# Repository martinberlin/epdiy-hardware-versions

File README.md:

# EPDiy Hardware 

Design files for [EPDiy](https://github.com/vroland/epdiy) controllers, controller variants, display adaptors, and other related hardware.  
See [vroland.github.io/epdiy-hardware/](https://vroland.github.io/epdiy-hardware/) for available hardware.

## What is EPDiy?

Please refer to the [main project repository](https://github.com/vroland/epdiy) for more information.

## Cloning

Make sure to clone recursively, to get hardware library submodules:
```
git clone git@github.com:vroland/epdiy-hardware.git --recursive
# or with http
git clone https://github.com/vroland/epdiy-hardware.git --recursive
```

## Contributing Hardware

Contributions in the form of adapter boards, utilities or epdiy variants are always welcome!
Please submit a PR and make sure your KiCAD project is in the right format, so our automation can build 
the manufacturing files and overview page:

* For every board, the KiCAD project should be given a unique name, and have the same name as the containing folder. 
  Example: `epdiy-v7/epdiy-v7.{kicad_pro,kicad_pcb,kicad_sch}`. 
  An existing KiCAD project can be renamed by selecting `File -> Save As` in the main KiCAD window and saving it to a folder with the new name.
* Unless you *explicitly* specify otherwise, your contribution will be licensed under the Creative Commons Attribution-ShareAlike 4.0 International License.
  Feel free to mention in the README in your project folder how you want to be attributed.
  Please indicate in the PR if you intend to use a different license.
* Each board needs a README.md in it's project folder, which will also appear as description in the presentation page.
  Refer to `epdiy-v7/README.md` for an example.
* If it's a helper or an adapter board, place it in the appropriate `helpers` or `adapters` folder.
* Delete the manufacturing files and keep only the sources.
  Since we generate those automatically, having potentially outdated ones in the repo will be confusing. 
* Add your board to the `BOARDS` list in the root `Makefile`.
  This enables the continuous integration to build the manufacturing files for your board.

## Available Hardware

The full list of available hardware is available at [vroland.github.io/epdiy-hardware/](https://vroland.github.io/epdiy-hardware/).
For each board, we provide:

- Gerber files
- Bill of Materials (BoM)
- Pick & Place Positioning file
- PDF Schematic
- 3D model of the board for use in CAD

## Related repositories

- [Check FastJsonDL](https://github.com/martinberlin/FastJsonDL) a JSON domain language to draw GFX on displays that could be sent from a webservice or from an AI agent.
- [vroland/epdiy](https://github.com/vroland/epdiy)

## Licensing

Unless otherwise specified, the hardware sources provided are licensed under the terms of the Creative Commons Attribution-ShareAlike 4.0 International License.
<a rel="license" href="https://creativecommons.org/licenses/by-sa/4.0/">Creative Commons Attribution-ShareAlike 4.0 International License </a>

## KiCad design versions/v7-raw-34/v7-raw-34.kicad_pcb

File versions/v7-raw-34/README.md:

### Epdiy V7 RAW

The V7 controller iteration is based on the ESP32S3. Highlights of the new board include:

- Much faster updates thanks to the ESP32S3 SOC and the LCD peripheral
- Front light support for Kindle / Kaleido 
- LiPo charging

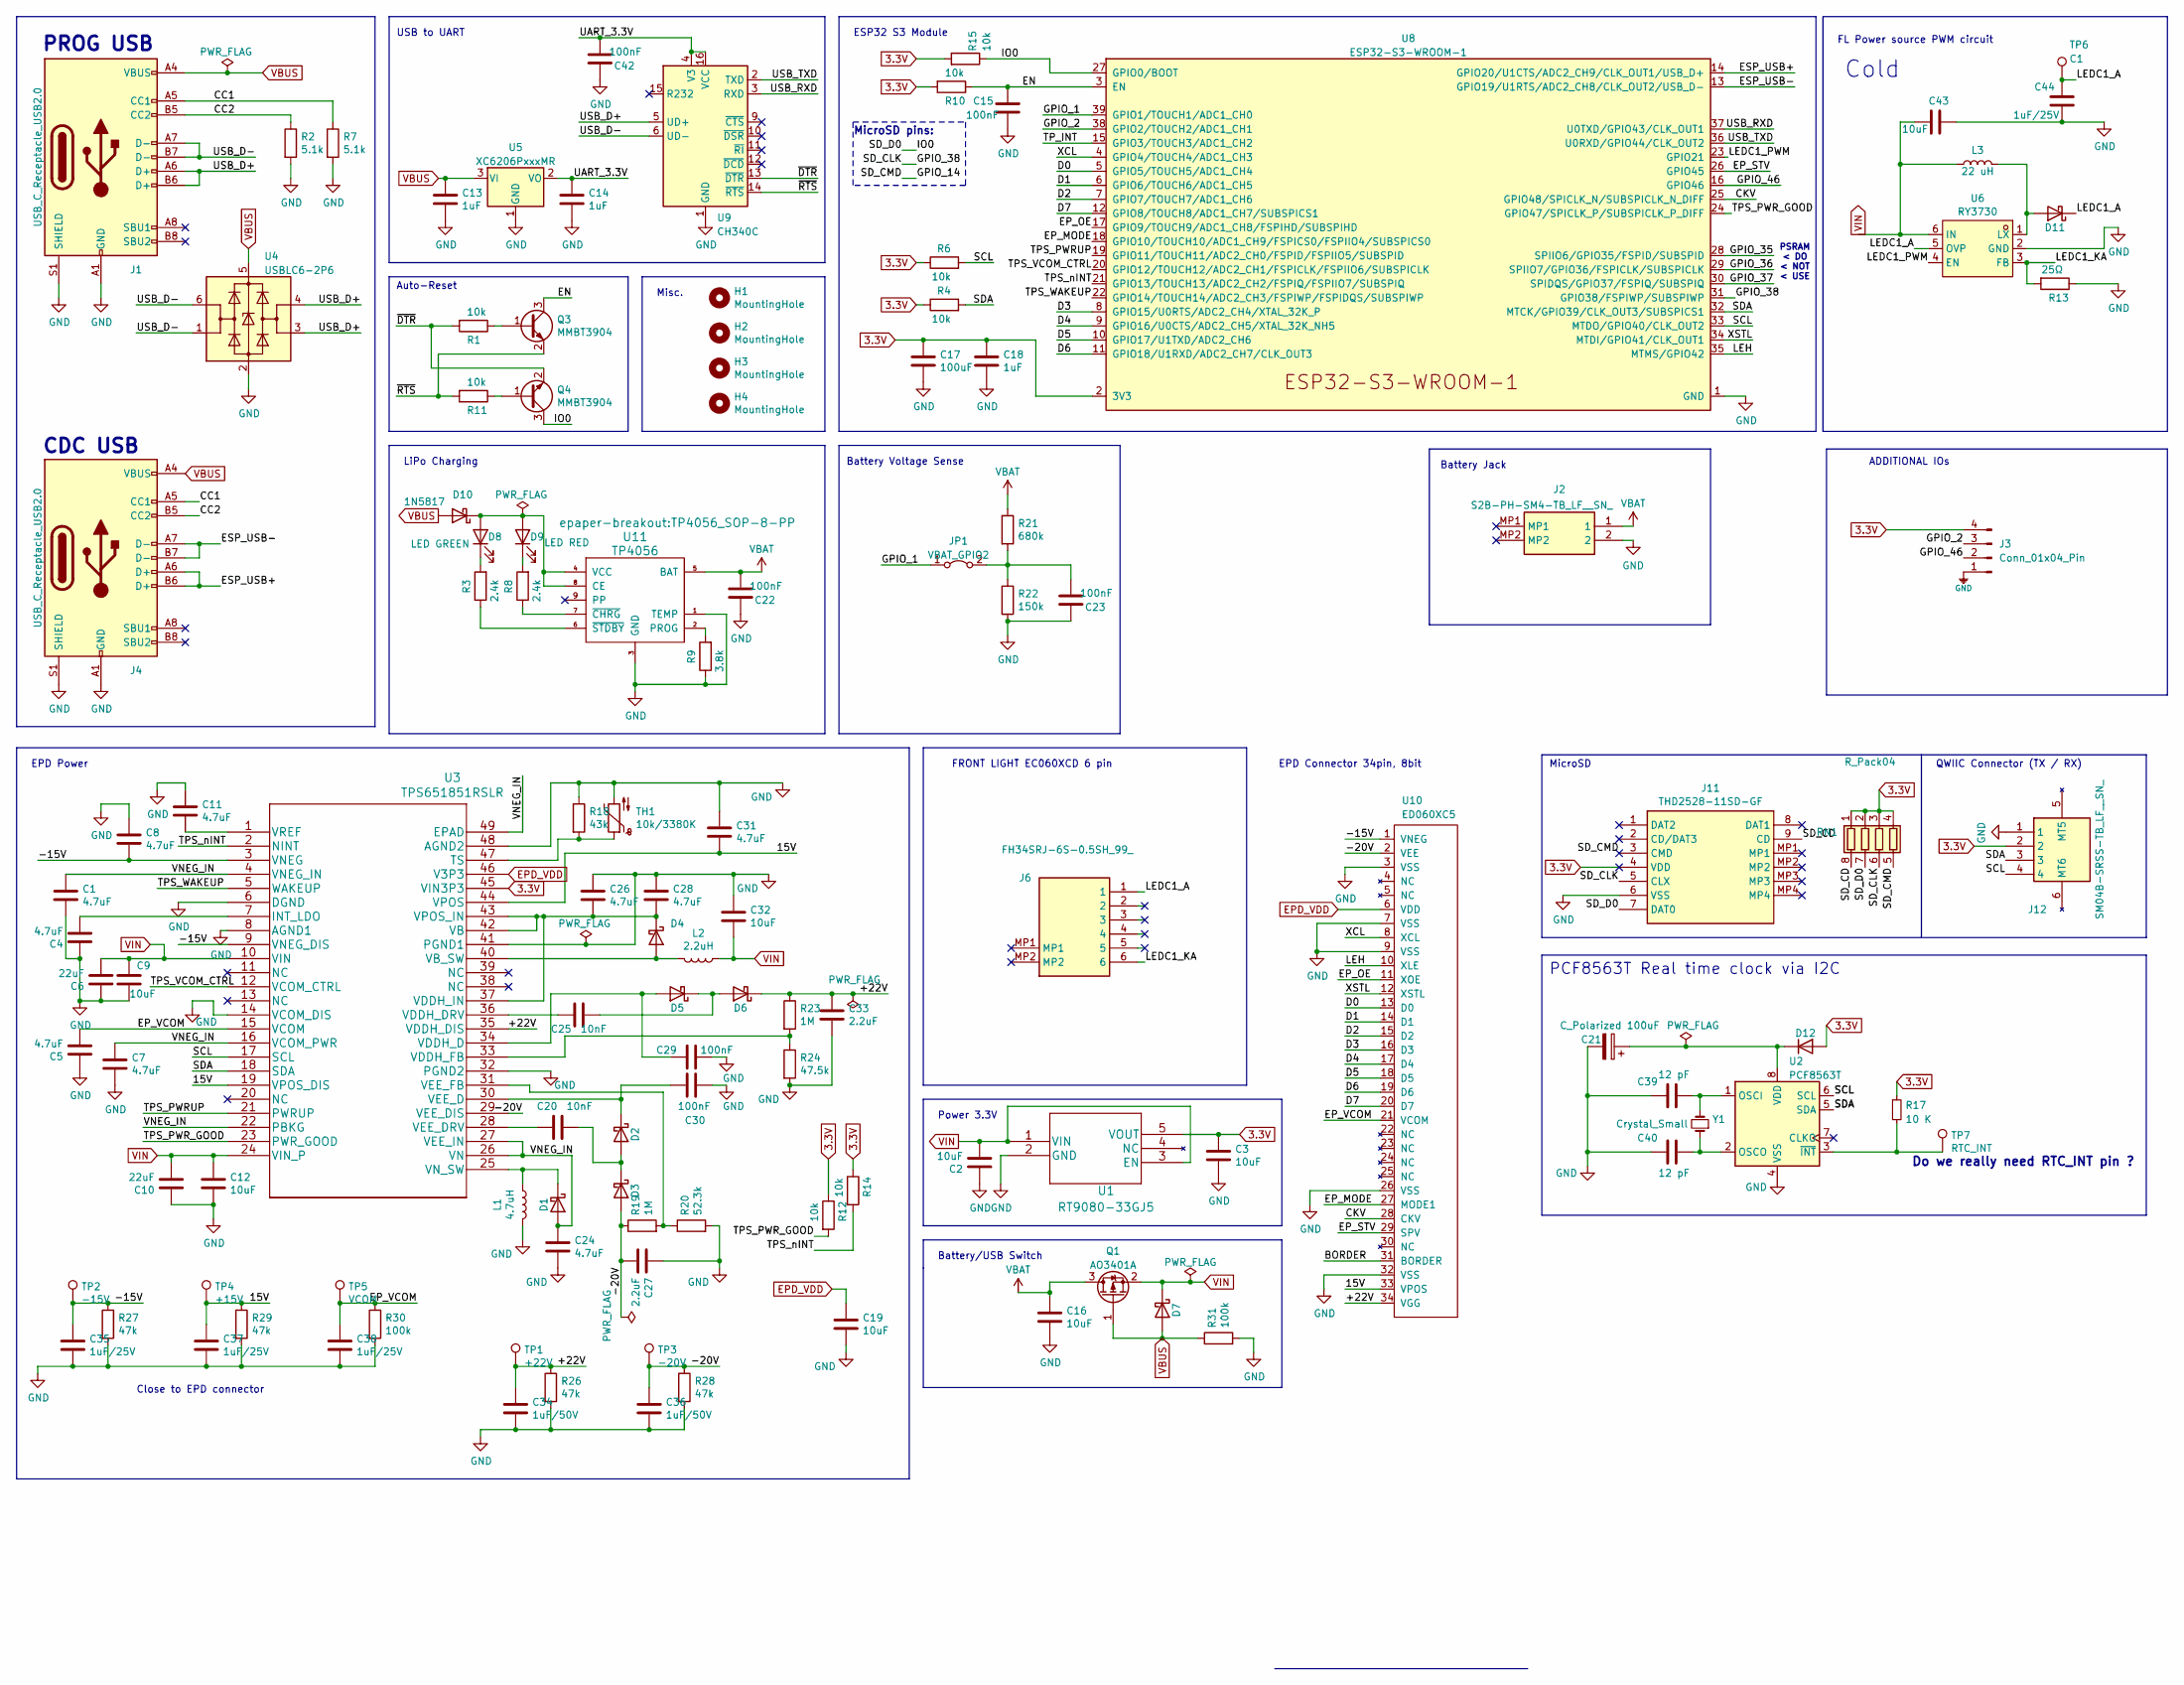
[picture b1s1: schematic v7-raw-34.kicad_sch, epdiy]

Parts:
C1, C4, C5, C7, C8, C11, C24, C26, C28, C31: 4.7uF; C_0805_2012Metric; LCSC C1779
C2, C3, C9, C12, C16, C19, C32, C43: 10uF; C_0805_2012Metric; LCSC C15850
C6, C10: 22uF; C_0805_2012Metric; LCSC C45783
C13, C14, C18: 1uF; C_0805_2012Metric; LCSC C28323
C15, C22, C23, C29, C30, C42: 100nF; C_0805_2012Metric; LCSC C49678
C17: 100uF; CP_EIA-3528-15_AVX-H; LCSC C16133
C20, C25: 10nF; C_0805_2012Metric; LCSC C1710
C21: C_Polarized 100uF; CP_EIA-3528-21_Kemet-B; LCSC C129289
C27, C33: 2.2uF; C_0805_2012Metric; LCSC C49217
C34, C36: 1uF/50V; C_1206_3216Metric; LCSC C1848
C35, C37, C38, C44: 1uF/25V; C_0805_2012Metric; LCSC C28323
C39, C40: 12 pF; C_0603_1608Metric; LCSC C38523
D1, D2, D3, D4, D5, D6, D7, D11: MBR0540; D_SOD-123; LCSC C21353
D8: LED GREEN; LED_0805_2012Metric; LCSC C2297
D9: LED RED; LED_0805_2012Metric; LCSC C84256
D10: 1N5817; D_SOD-123; LCSC C8598
D12: 1N4148WS; D_SOD-323; LCSC C2128
H1, H2, H3, H4: MountingHole; MountingHole_2.2mm_M2
J1, J4: USB_C_Receptacle_USB2.0; USB_C_Receptacle_HRO_TYPE-C-31-M-12; LCSC C165948
J2: S2B-PH-SM4-TB_LF__SN_; S2BPHSM4TBLFSN; Manufacturer_Part_Number S2B-PH-SM4-TB(LF)(SN); LCSC C295747
J3: Conn_01x04_Pin; PinHeader_1x04_P2.54mm_Vertical
J6: FH34SRJ-6S-0.5SH_99_; C224194_6x1_FH34SRJ-6S-0.5SH50_HIR; Manufacturer_Part_Number FH34SRJ-6S-0.5SH(99); Mouser Part Number 798-FH34SRJ6S0.5SH99
J11: THD2528-11SD-GF; THD252811SDGF; Manufacturer_Part_Number THD2528-11SD-GF; LCSC C283232
J12: SM04B-SRSS-TB_LF__SN_; QWIIC_SM04B-SRSS-TB_LFSN_; Manufacturer_Part_Number SM04B-SRSS-TB(LF)(SN); LCSC C160404
JP1: VBAT_GPIO2; SolderJumper-2_P1.3mm_Bridged2Bar_Pad1.0x1.5mm
L1: 4.7uH; L_Taiyo-Yuden_NR-50xx_HandSoldering; LCSC C222947
L2: 2.2uH; L_Taiyo-Yuden_NR-40xx_HandSoldering; LCSC C92959
L3: 22 uH; SWPA5040S282MT; LCSC C68434
Q1: AO3401A; SOT-23; LCSC C15127
Q3, Q4: MMBT3904; SOT-23; LCSC C20526
R1, R4, R6, R10, R11, R12, R14, R15: 10k; R_0603_1608Metric; LCSC C25804
R2, R7: 5.1k; R_0603_1608Metric; LCSC C23186
R3, R8: 2.4k; R_0603_1608Metric; LCSC C22940
R9: 3.8k; R_0603_1608Metric; LCSC C103591
R13: 25Ω; R_0603_1608Metric; LCSC C308324
R17: 10 K; R_0603_1608Metric; LCSC C25804
R18: 43k; R_0603_1608Metric; LCSC C23172
R19, R23: 1M; R_0603_1608Metric; LCSC C22935
R20: 52.3k; R_0603_1608Metric; LCSC C23196
R21: 680k; R_0603_1608Metric; LCSC C25822
R22: 150k; R_0603_1608Metric; LCSC C22807
R24: 47.5k; R_0603_1608Metric; LCSC C25819
R26, R27, R28, R29: 47k; R_0603_1608Metric; LCSC C25819
R30, R31: 100k; R_0603_1608Metric; LCSC C25803
RN1: R_Pack04; C425297_RES-ARRAY-SMD_0402-8P-L2.0-W1.0-BL; LCSC C425297
TH1: 10k/3380K; R_0603_1608Metric; LCSC C76589
TP1: +22V; TestPoint_Pad_D2.5mm
TP2: -15V; TestPoint_Pad_D2.5mm
TP3: -20V; TestPoint_Pad_D2.5mm
TP4: +15V; TestPoint_Pad_D2.5mm
TP5: VCOM; TestPoint_Pad_D2.5mm
TP6: C1; TestPoint_Pad_D2.5mm
TP7: RTC_INT; TestPoint_Pad_D1.5mm
U1: RT9080-33GJ5; TSOT-23-5; LCSC C841192
U2: PCF8563T; SOIC-8_3.9x4.9mm_P1.27mm; LCSC C7440
U3: TPS651851RSLR; LCSC C139292
U4: USBLC6-2P6; SOT-666; LCSC C2827693
U5: XC6206PxxxMR; SOT-23-3; LCSC C5446
U6: RY3730; SOT-23-6_RY3730_Led_PWM; LCSC C370887
U8: ESP32-S3-WROOM-1; LCSC C2913202
U9: CH340C; SOIC-16_3.9x9.9mm_P1.27mm; LCSC C84681
U10: ED060XC5; X05A20H34G; LCSC C528053
U11: TP4056; TP4056_SOP-8-PP; LCSC C16581
Y1: Crystal_Small; Q13FC1350000400-Crystal; LCSC C32346

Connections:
3.3V: C3.2, C17.1, C18.2, D12.2 (A), J3.4, J11.4 (VDD), J12.2, R4.1, R6.1, R10.2, R12.1, R14.1, R15.2, R17.1, RN1.1 (R1.1), RN1.2 (R2.1), RN1.3 (R3.1), RN1.4 (R4.1), U1.5 (VOUT), U3.45 (VIN3P3), U8.2 (3V3)
/15V: C31.2, C37.1, R29.1, TP4.1 (1_1), U3.19 (VPOS_DIS), U3.44 (VPOS), U10.33 (VPOS)
/+22V: C33.1, C34.1, D6.1 (K), R23.1, R26.1, TP1.1 (1_1), U3.35 (VDDH_DIS), U10.34 (VGG)
/-15V: C8.2, C35.1, R27.1, TP2.1 (1_1), U3.3 (VNEG), U3.9 (VNEG_DIS), U10.1 (VNEG)
/-20V: C27.2, C36.1, D3.2 (A), R19.1, R28.1, TP3.1 (1_1), U3.29 (VEE_DIS), U10.2 (VEE)
/BORDER: U10.31 (BORDER)
/CC1: J1.A5 (CC1), J4.A5 (CC1), R7.1
/CC2: J1.B5 (CC2), J4.B5 (CC2), R2.1
/CKV: U8.25 (GPIO48/SPICLK_N/SUBSPICLK_N_DIFF), U10.28 (CKV)
/D0: U8.5 (GPIO5/TOUCH5/ADC1_CH4), U10.13 (D0)
/D1: U8.6 (GPIO6/TOUCH6/ADC1_CH5), U10.14 (D1)
/D2: U8.7 (GPIO7/TOUCH7/ADC1_CH6), U10.15 (D2)
/D3: U8.8 (GPIO15/U0RTS/ADC2_CH4/XTAL_32K_P), U10.16 (D3)
/D4: U8.9 (GPIO16/U0CTS/ADC2_CH5/XTAL_32K_NH5), U10.17 (D4)
/D5: U8.10 (GPIO17/U1TXD/ADC2_CH6), U10.18 (D5)
/D6: U8.11 (GPIO18/U1RXD/ADC2_CH7/CLK_OUT3), U10.19 (D6)
/D7: U8.12 (GPIO8/TOUCH8/ADC1_CH7/SUBSPICS1), U10.20 (D7)
/EN: C15.1, Q3.3 (C), R10.1, U8.3 (EN)
/EP_MODE: U8.18 (GPIO10/TOUCH10/ADC1_CH9/FSPICS0/FSPIIO4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), U10.27 (MODE1)
/EP_OE: U8.17 (GPIO9/TOUCH9/ADC1_CH8/FSPIHD/SUBSPIHD), U10.11 (XOE)
/EP_STV: U8.26 (GPIO45), U10.29 (SPV)
/EP_VCOM: C5.2, C38.1, R30.1, TP5.1 (1_1), U3.15 (VCOM), U10.21 (VCOM)
/ESP_USB+: J4.A6 (D+), J4.B6 (D+), U8.14 (GPIO20/U1CTS/ADC2_CH9/CLK_OUT1/USB_D+)
/ESP_USB-: J4.A7 (D-), J4.B7 (D-), U8.13 (GPIO19/U1RTS/ADC2_CH8/CLK_OUT2/USB_D-)
/GPIO_1: JP1.1 (A), U8.39 (GPIO1/TOUCH1/ADC1_CH0)
/GPIO_2: J3.3, U8.38 (GPIO2/TOUCH2/ADC1_CH1)
/GPIO_14: J11.3 (CMD), RN1.5 (R4.2)
/GPIO_35: U8.28 (SPIIO6/GPIO35/FSPID/SUBSPID)
/GPIO_36: U8.29 (SPIIO7/GPIO36/FSPICLK/SUBSPICLK)
/GPIO_37: U8.30 (SPIDQS/GPIO37/FSPIQ/SUBSPIQ)
/GPIO_38: J11.5 (CLX), RN1.6 (R3.2), U8.31 (GPIO38/FSPIWP/SUBSPIWP)
/GPIO_46: J3.2, U8.16 (GPIO46)
/IO0: J11.7 (DAT0), Q4.3 (C), R15.1, RN1.7 (R2.2), U8.27 (GPIO0/BOOT)
/LEDC1_A: C44.1, D11.1 (K), J6.1, TP6.1 (1_1), U6.5 (OVP)
/LEDC1_KA: J6.6, R13.2, U6.3 (FB)
/LEDC1_PWM: U6.4 (EN), U8.23 (GPIO21)
/LEH: U8.35 (MTMS/GPIO42), U10.10 (XLE)
/SCL: J12.4, R6.2, U2.6 (SCL), U3.17 (SCL), U8.33 (MTDO/GPIO40/CLK_OUT2)
/SDA: J12.3, R4.2, U2.5 (SDA), U3.18 (SDA), U8.32 (MTCK/GPIO39/CLK_OUT3/SUBSPICS1)
/SD_CD: J11.9 (CD), RN1.8 (R1.2)
/TPS_PWRUP: U3.21 (PWRUP), U8.19 (GPIO11/TOUCH11/ADC2_CH0/FSPID/FSPIIO5/S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)
/TPS_PWR_GOOD: R12.2, U3.23 (PWR_GOOD), U8.24 (GPIO47/SPICLK_P/SUBSPICLK_P_DIFF)
/TPS_VCOM_CTRL: U3.12 (VCOM_CTRL), U8.20 (GPIO12/TOUCH12/ADC2_CH1/FSPICLK/FSPIIO6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)
/TPS_WAKEUP: U3.5 (WAKEUP), U8.22 (GPIO14/TOUCH14/ADC2_CH3/FSPIWP/FSPIDQS/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)
/TPS_nINT: R14.2, U3.2 (NINT), U8.21 (GPIO13/TOUCH13/ADC2_CH2/FSPIQ/FSPIIO7/S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)
/TP_INT: U8.15 (GPIO3/TOUCH3/ADC1_CH2)
/UART_3.3V: C14.2, C42.2, U5.2 (VO), U9.4 (V3), U9.16 (VCC)
/USB_D+: J1.A6 (D+), J1.B6 (D+), U4.3 (I/O2), U4.4 (I/O2), U9.5 (UD+)
/USB_D-: J1.A7 (D-), J1.B7 (D-), U4.1 (I/O1), U4.6 (I/O1), U9.6 (UD-)
/USB_RXD: U8.37 (U0TXD/GPIO43/CLK_OUT1), U9.3 (RXD)
/USB_TXD: U8.36 (U0RXD/GPIO44/CLK_OUT2), U9.2 (TXD)
/VNEG_IN: C1.1, C7.1, C24.1, D1.2 (A), U3.4 (VNEG_IN), U3.16 (VCOM_PWR), U3.22 (PBKG), U3.26 (VN), U3.27 (VEE_IN), U3.49 (EPAD)
/XCL: U8.4 (GPIO4/TOUCH4/ADC1_CH3), U10.8 (XCL)
/XSTL: U8.34 (MTDI/GPIO41/CLK_OUT1), U10.12 (XSTL)
/~DTR: Q4.2 (E), R1.2, U9.13 (~DTR)
/~RTS: Q3.2 (E), R11.2, U9.14 (~RTS)
EPD_VDD: C19.1, U3.46 (V3P3), U10.6 (VDD)
unnamed: D1.1 (K), L1.1, U3.25 (VN_SW)
unnamed: C20.1, D2.2 (A), D3.1 (K)
unnamed: C30.1, D2.1 (K), U3.30 (VEE_D)
unnamed: D4.2 (A), L2.2, U3.40 (VB_SW)
unnamed: C26.2, C28.2, D4.1 (K), U3.37 (VDDH_IN), U3.42 (VB), U3.43 (VPOS_IN)
unnamed: C29.2, D5.2 (A), U3.34 (VDDH_D)
unnamed: C25.1, D5.1 (K), D6.2 (A)
unnamed: D8.1 (K), R3.2
unnamed: D9.1 (K), R8.2
unnamed: D8.2 (A), D9.2 (A), D10.1 (K), U11.4 (VCC), U11.8 (CE)
unnamed: D11.2 (A), L3.2, U6.1 (LX)
unnamed: C21.1, D12.1 (K), U2.8 (VDD)
unnamed: C23.2, JP1.2 (B), R21.2, R22.1
unnamed: Q3.1 (B), R1.1
unnamed: Q4.1 (B), R11.1
unnamed: C39.2, U2.1 (OSCI), Y1.2
unnamed: C40.2, U2.2 (OSCO), Y1.1
unnamed: R17.2, TP7.1 (1_1), U2.3 (~INT)
unnamed: C4.2, U3.7 (INT_LDO)
unnamed: R18.2, TH1.1, U3.47 (TS)
unnamed: C25.2, U3.36 (VDDH_DRV)
unnamed: R23.2, R24.1, U3.33 (VDDH_FB)
unnamed: C20.2, U3.28 (VEE_DRV)
unnamed: R19.2, R20.1, U3.31 (VEE_FB)
unnamed: C11.2, U3.1 (VREF)
unnamed: R9.2, U11.2 (PROG)
unnamed: R8.1, U11.7 (~CHRG)
unnamed: R3.1, U11.6 (~STDBY)
VBAT: C16.2, C22.2, J2.1, Q1.3 (D), R21.1, U11.5 (BAT)
VIN: C2.1, C6.2, C9.1, C10.2, C12.1, C32.2, C43.2, D7.1 (K), L2.1, L3.1, Q1.2 (S), U1.1 (VIN), U1.3 (EN), U3.10 (VIN), U3.24 (VIN_P), U6.6 (IN)

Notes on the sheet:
Battery Voltage Sense
Misc.
EPD Power
PCF8563T Real time clock via I2C
Do we really need RTC_INT pin ?
QWIIC Connector (TX / RX)
ESP32 S3 Module
PROG USB
Power 3.3V
Auto-Reset
MicroSD pins:
ADDITIONAL IOs
Battery/USB Switch
USB to UART
CDC USB
EPD Connector 34pin, 8bit
PSRAM < DO < NOT < USE
FRONT LIGHT EC060XCD 6 pin
FL Power source PWM circuit
Cold
MicroSD
Battery Jack
LiPo Charging
Close to EPD connector

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
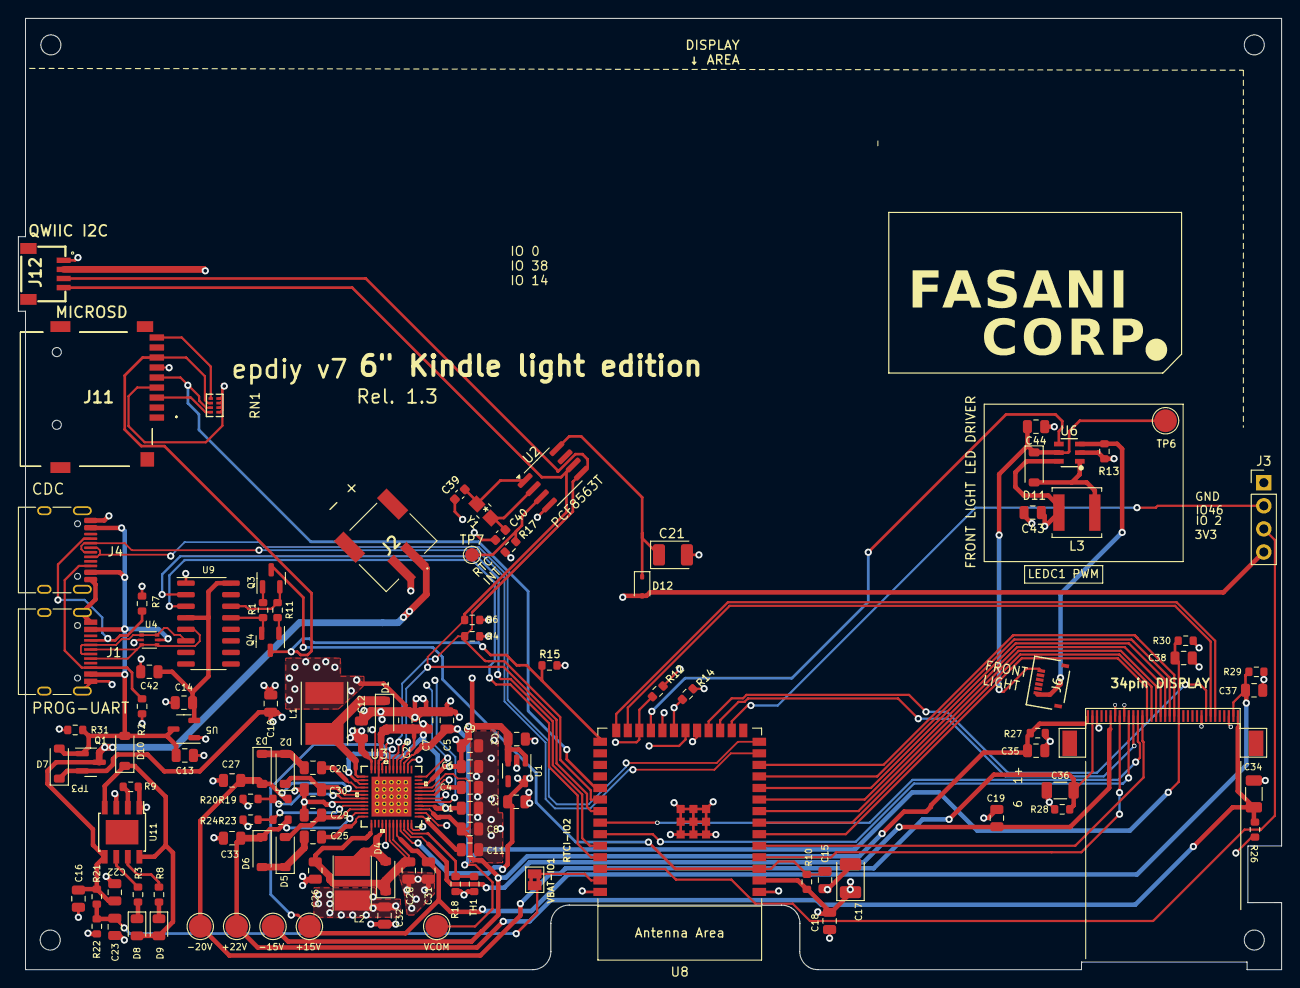
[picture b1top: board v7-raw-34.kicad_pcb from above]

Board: 4 copper layers, 138.9 x 104.6 mm, 121 parts (0 on the bottom side), 84 nets.

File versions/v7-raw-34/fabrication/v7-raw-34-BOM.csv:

Comment,Designator,Footprint,LCSC
4.7uF,"C1,C4,C5,C7,C8,C11,C24,C26,C28,C31",Capacitor_SMD:C_0805_2012Metric,C1779
1uF,"C13,C14,C18",Capacitor_SMD:C_0805_2012Metric,C28323
100nF,"C15,C22,C23,C29,C30,C42",Capacitor_SMD:C_0805_2012Metric,C49678
100uF,C17,Capacitor_Tantalum_SMD:CP_EIA-3528-15_AVX-H,C16133
10uF,"C2,C3,C9,C12,C16,C19,C32,C43",Capacitor_SMD:C_0805_2012Metric,C15850
10nF,"C20,C25",Capacitor_SMD:C_0805_2012Metric,C1710
C_Polarized 100uF,C21,Capacitor_Tantalum_SMD:CP_EIA-3528-21_Kemet-B,C129289
2.2uF,"C27,C33",Capacitor_SMD:C_0805_2012Metric,C49217
1uF/50V,"C34,C36",Capacitor_SMD:C_1206_3216Metric,C1848
1uF/25V,"C35,C37,C38,C44",Capacitor_SMD:C_0805_2012Metric,C28323
12 pF,"C39,C40",Capacitor_SMD:C_0603_1608Metric,C38523
22uF,"C6,C10",Capacitor_SMD:C_0805_2012Metric,C45783
MBR0540,"D1,D2,D3,D4,D5,D6,D7,D11",Diode_SMD:D_SOD-123,C21353
1N5817,D10,Diode_SMD:D_SOD-123,C8598
1N4148WS,D12,Diode_SMD:D_SOD-323,C2128
LED GREEN,D8,LED_SMD:LED_0805_2012Metric,C2297
LED RED,D9,LED_SMD:LED_0805_2012Metric,C84256
USB_C_Receptacle_USB2.0,"J1,J4",Connector_USB:USB_C_Receptacle_HRO_TYPE-C-31-M-12,C165948
THD2528-11SD-GF,J11,THD252811SDGF,C283232
S2B-PH-SM4-TB_LF__SN_,J2,footprint:S2BPHSM4TBLFSN,C295747
FH34SRJ-6S-0.5SH_99_,J6,footprint:C224194_6x1_FH34SRJ-6S-0.5SH50_HIR,C224194
4.7uH,L1,Inductor_SMD:L_Taiyo-Yuden_NR-50xx_HandSoldering,C222947
2.2uH,L2,Inductor_SMD:L_Taiyo-Yuden_NR-40xx_HandSoldering,C92959
22 uH,L3,footprint:SWPA5040S282MT,C68434
AO3401A,Q1,Package_TO_SOT_SMD:SOT-23,C15127
MMBT3904,"Q3,Q4",Package_TO_SOT_SMD:SOT-23,C20526
10k,"R1,R4,R6,R10,R11,R12,R14,R15",Resistor_SMD:R_0603_1608Metric,C25804
25Ω,R13,Resistor_SMD:R_0603_1608Metric,C308324
10 K,R17,Resistor_SMD:R_0603_1608Metric,C25804
43k,R18,Resistor_SMD:R_0603_1608Metric,C23172
1M,"R19,R23",Resistor_SMD:R_0603_1608Metric,C22935
5.1k,"R2,R7",Resistor_SMD:R_0603_1608Metric,C23186
52.3k,R20,Resistor_SMD:R_0603_1608Metric,C23196
680k,R21,Resistor_SMD:R_0603_1608Metric,C25822
150k,R22,Resistor_SMD:R_0603_1608Metric,C22807
47.5k,R24,Resistor_SMD:R_0603_1608Metric,C25819
47k,"R26,R27,R28,R29",Resistor_SMD:R_0603_1608Metric,C25819
2.4k,"R3,R8",Resistor_SMD:R_0603_1608Metric,C22940
100k,"R30,R31",Resistor_SMD:R_0603_1608Metric,C25803
0R,"R5,R16",Resistor_SMD:R_0603_1608Metric,C21189
3.8k,R9,Resistor_SMD:R_0603_1608Metric,C103591
R_Pack04,RN1,footprint:RESN_F392JTCE_UNR_SD-pullup,C425297
10k/3380K,TH1,Resistor_SMD:R_0603_1608Metric,C76589
RT9080-33GJ5,U1,Package_TO_SOT_SMD:TSOT-23-5,C841192
ED060XC5,U10,epaper-breakout:X05A20H34G,C528053
TP4056,U11,epaper-breakout:TP4056_SOP-8-PP,C16581
PCF8563T,U2,Package_SO:SOIC-8_3.9x4.9mm_P1.27mm,C7440
TPS651851RSLR,U3,footprint:TPS651851RSLR,C139292
USBLC6-2P6,U4,Package_TO_SOT_SMD:SOT-666,C2827693
XC6206PxxxMR,U5,Package_TO_SOT_SMD:SOT-23-3,C5446
RY3730,U6,footprint:SOT-23-6_RY3730_Led_PWM,C370887
ESP32-S3-WROOM-1,U8,Espressif:ESP32-S3-WROOM-1,C2913202
CH340C,U9,Package_SO:SOIC-16_3.9x9.9mm_P1.27mm,C84681
Crystal_Small,Y1,footprint:Q13FC1350000400-Crystal,C32346
SM04B-SRSS-TB_LFSN_,J12,QWIIC_SM04B-SRSS-TB_LFSN_,C160404

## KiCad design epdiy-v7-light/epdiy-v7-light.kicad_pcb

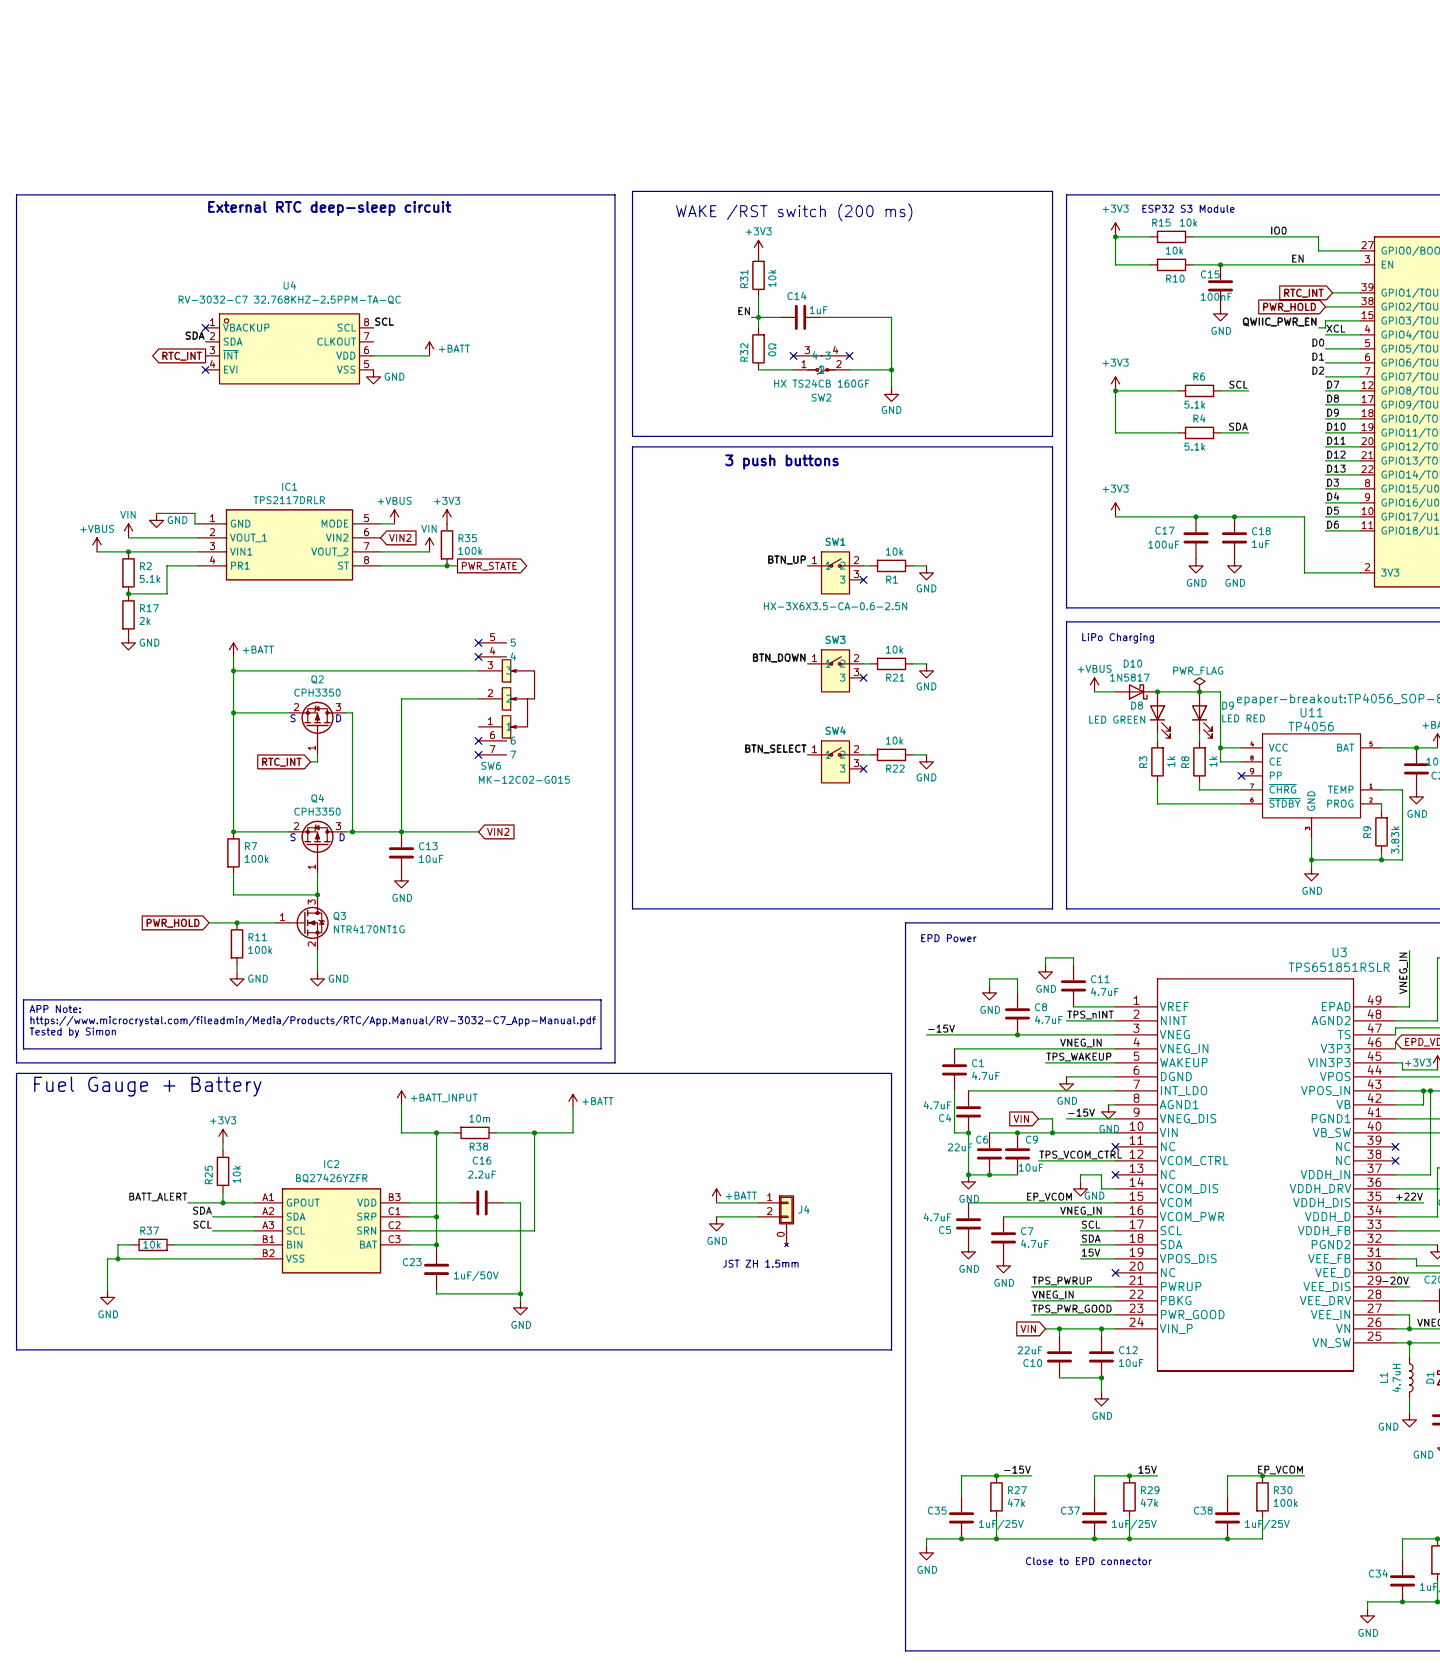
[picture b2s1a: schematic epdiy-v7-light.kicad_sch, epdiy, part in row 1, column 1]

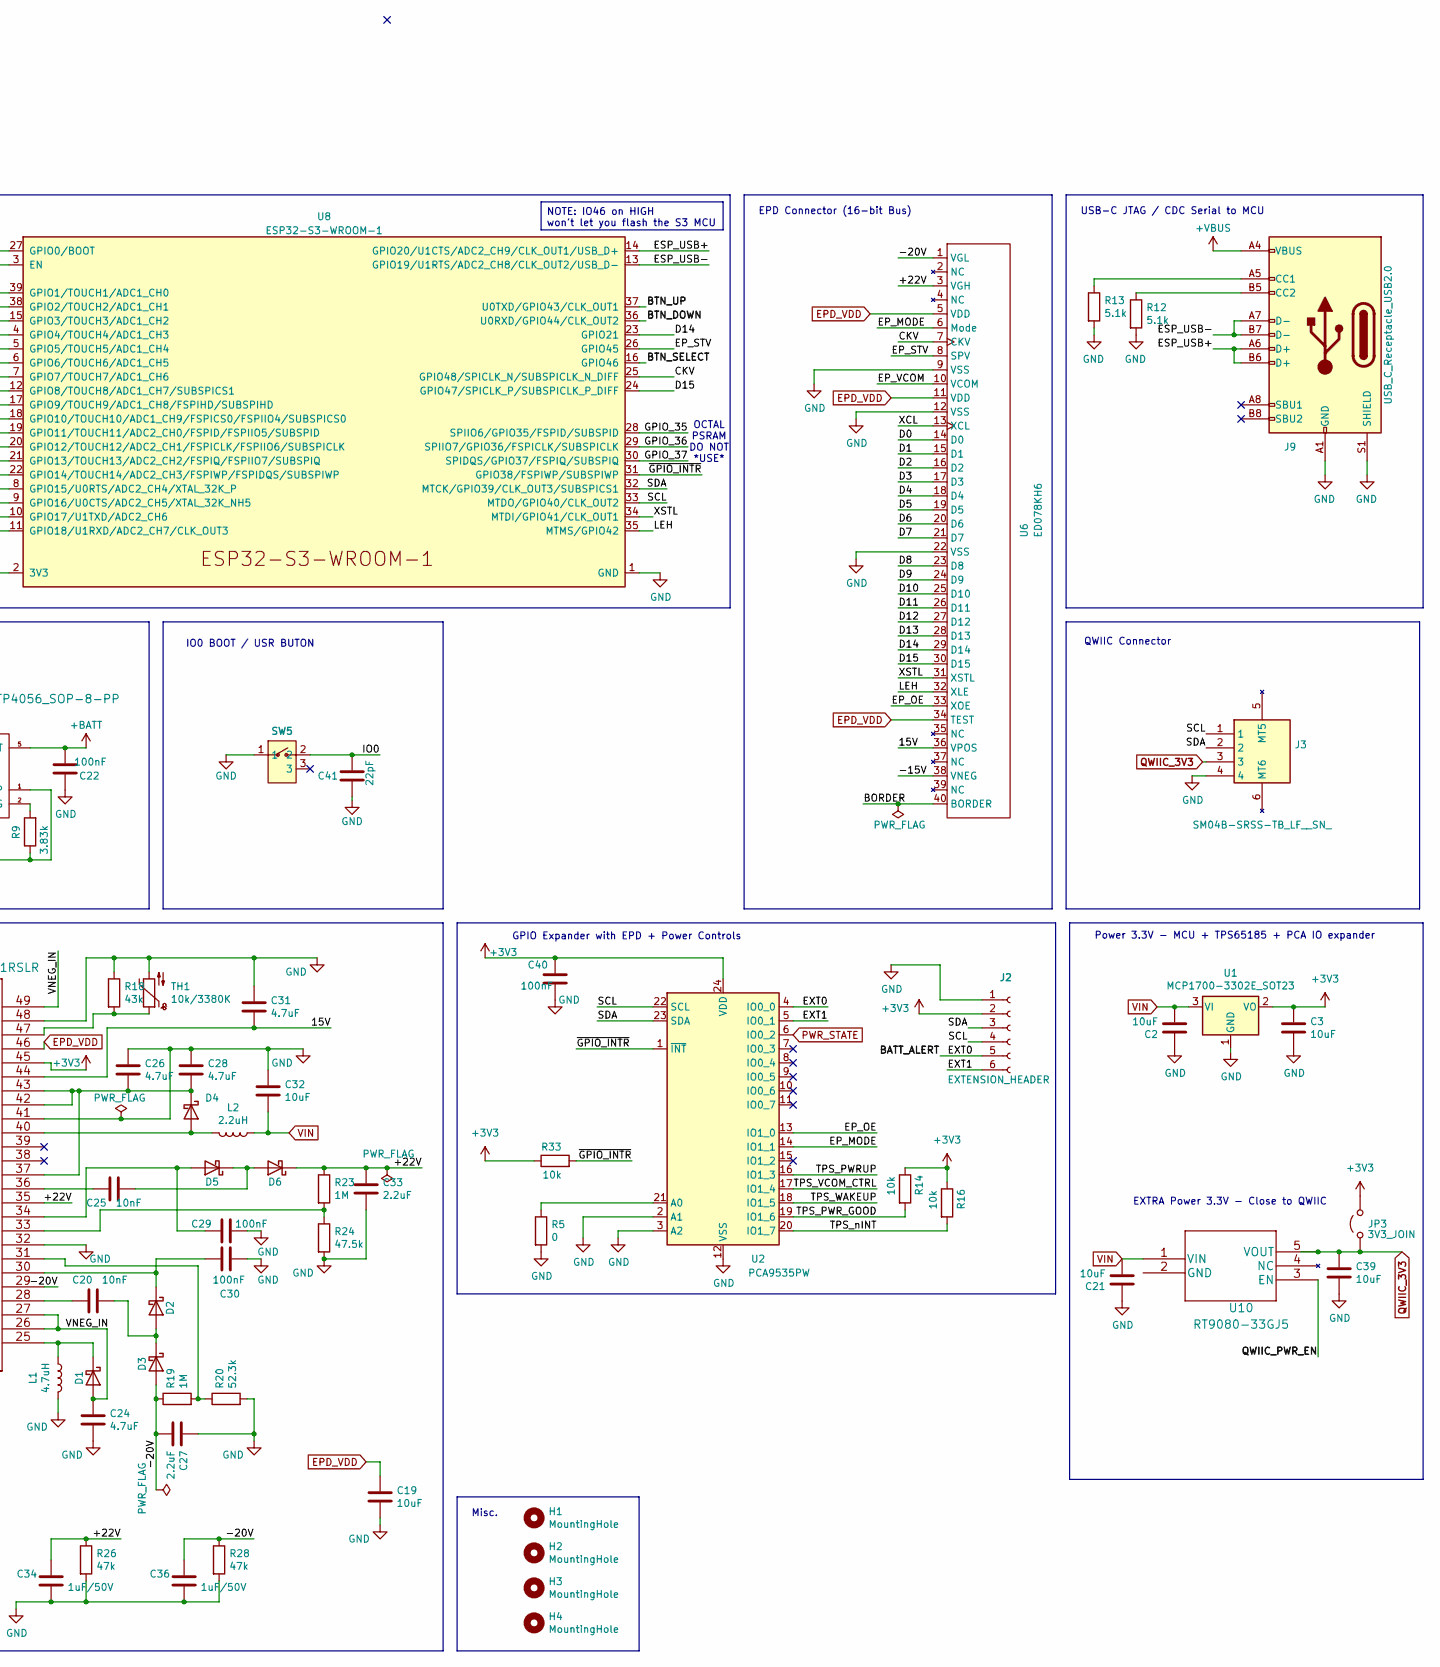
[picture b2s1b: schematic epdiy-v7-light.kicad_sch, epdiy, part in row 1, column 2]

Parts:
C1, C4, C5, C7, C8, C11, C24, C26, C28, C31: 4.7uF; C_0805_2012Metric; LCSC C1779
C2, C3, C9, C12, C13, C19, C21, C32, C39: 10uF; C_0805_2012Metric; LCSC C15850
C6, C10: 22uF; C_0805_2012Metric; LCSC C45783
C14: 1uF; C_0402_1005Metric; LCSC C162161
C15, C22, C29, C30, C40: 100nF; C_0805_2012Metric; LCSC C49678
C16, C27, C33: 2.2uF; C_0805_2012Metric; LCSC C49217
C17: 100uF; CP_EIA-3528-15_AVX-H; LCSC C16133
C18: 1uF; C_0805_2012Metric; LCSC C28323
C20, C25: 10nF; C_0805_2012Metric; LCSC C1710
C23, C34, C36: 1uF/50V; C_1206_3216Metric; LCSC C1848
C35, C37, C38: 1uF/25V; C_0805_2012Metric; LCSC C28323
C41: 22pF; C_0402_1005Metric; LCSC C5119318
D1, D2, D3, D4, D5, D6: MBR0540; D_SOD-123; LCSC C21353
D8: LED GREEN; LED_0805_2012Metric; LCSC C2297
D9: LED RED; LED_0805_2012Metric; LCSC C84256
D10: 1N5817; D_SOD-123; LCSC C8598
H1, H2, H3, H4: MountingHole; MountingHole_2.2mm_M2
IC1: TPS2117DRLR; C22399676_TPS2117-8N; LCSC C3235557
IC2: BQ27426YZFR; Texas_DSBGA-9_1.62x1.58mm_Layout3x3_P0.5mm; LCSC C165137
J2: EXTENSION_HEADER; PinHeader_1x06_P2.54mm_Vertical
J3: SM04B-SRSS-TB_LF__SN_; QWIIC_SM04B-SRSS-TB_LFSN_; Manufacturer_Part_Number SM04B-SRSS-TB(LF)(SN); LCSC C160404
J4: Conn_01x02_Shielded; C265329_BATT_S2B-ZR-SM4A; LCSC C265329
J9: USB_C_Receptacle_USB2.0; USB_C_Receptacle_HRO_TYPE-C-31-M-12; LCSC C165948
JP3: 3V3_JOIN; SolderJumper-2_P1.3mm_Open_RoundedPad1.0x1.5mm
L1: 4.7uH; L_Taiyo-Yuden_NR-50xx_HandSoldering; LCSC C222947
L2: 2.2uH; L_Taiyo-Yuden_NR-40xx_HandSoldering; LCSC C92959
Q2, Q4: CPH3350; SOT-23; LCSC C7494437
Q3: NTR4170NT1G; SOT-23; LCSC C236116
R1, R21, R22, R31: 10k; R_0402_1005Metric; LCSC C4322213
R2, R4, R6, R12, R13: 5.1k; R_0603_1608Metric; LCSC C23186
R3, R8: 1k; R_0603_1608Metric; LCSC C21190
R5: 0; R_0603_1608Metric; LCSC C21189
R7, R30: 100k; R_0603_1608Metric; LCSC C25803
R9: 3.83k; R_0603_1608Metric; LCSC C103591
R10, R14, R15, R16, R25, R33, R37: 10k; R_0603_1608Metric; LCSC C25804
R11, R35: 100k; R_0402_1005Metric; LCSC C102750
R17: 2k; R_0402_1005Metric; LCSC C4109
R18: 43k; R_0603_1608Metric; LCSC C23172
R19, R23: 1M; R_0603_1608Metric; LCSC C22935
R20: 52.3k; R_0603_1608Metric; LCSC C23196
R24: 47.5k; R_0603_1608Metric; LCSC C25819
R26, R27, R28, R29: 47k; R_0603_1608Metric; LCSC C25819
R32: 0Ω; R_0603_1608Metric; LCSC C21189
R38: 10m; R_2512_6332Metric; LCSC C323803
SW1, SW5: HX-3X6X3.5-CA-0.6-2.5N; SW-SMD_HX-3X6X3.5-CA-0.6-2.5N; LCSC C49234146
SW2: HX TS24CB 160GF; C25168832_TS24CB-160GF; LCSC C25168832
SW3, SW4: HX-3X6X3.5-CA-0.6-2.5N; SW-SMD_HX-3X6X3.5-CA-0.6-2.5N; LCSC Part C49234146
SW6: MK-12C02-G015; C963206_MK-12C02-G020; LCSC C963206
TH1: 10k/3380K; R_0603_1608Metric; LCSC C76589
U1: MCP1700-3302E_SOT23; SOT-23; LCSC C39051
U2: PCA9535PW; TSSOP-24_4.4x7.8mm_P0.65mm; LCSC C255606
U3: TPS651851RSLR; LCSC C139292
U4: RV-3032-C7 32.768KHZ-2.5PPM-TA-QC; C5127802_RV3032; LCSC C5127802
U6: ED078KH6; FH1240S05SH55_MIRRORED; LCSC C202114
U8: ESP32-S3-WROOM-1; LCSC C2913202
U10: RT9080-33GJ5; TSOT-23-5; LCSC C841192
U11: TP4056; TP4056_SOP-8-PP; LCSC C16581

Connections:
+3V3: C3.2, C17.1, C18.2, C40.1, J2.2, JP3.2 (B), R4.1, R6.1, R10.2, R14.1, R15.2, R16.1, R25.2, R31.2, R33.1, R35.1, U1.2 (VO), U2.24 (VDD), U3.45 (VIN3P3), U8.2 (3V3)
+BATT: C22.2, IC2.C2 (SRN), J4.1, Q2.2 (S), Q4.2 (S), R7.1, R38.1, SW6.3, U4.6 (VDD), U11.5 (BAT)
+BATT_INPUT: C23.1, IC2.C1 (SRP), IC2.C3 (BAT), R38.2
+VBUS: D10.2 (A), IC1.3 (VIN1), IC1.5 (MODE), J9.A4 (VBUS), J9.A9 (VBUS), J9.B4 (VBUS), J9.B9 (VBUS), R2.1
/15V: C31.2, C37.1, R29.1, U3.19 (VPOS_DIS), U3.44 (VPOS), U6.36 (VPOS)
/+22V: C33.1, C34.1, D6.1 (K), R23.1, R26.1, U3.35 (VDDH_DIS), U6.3 (VGH)
/-15V: C8.2, C35.1, R27.1, U3.3 (VNEG), U3.9 (VNEG_DIS), U6.38 (VNEG)
/-20V: C27.2, C36.1, D3.2 (A), R19.1, R28.1, U3.29 (VEE_DIS), U6.1 (VGL)
/BATT_ALERT: IC2.A1 (GPOUT), J2.5, R25.1, U2.4 (IO0_0)
/BTN_DOWN: SW3.1, U8.36 (U0RXD/GPIO44/CLK_OUT2)
/BTN_SELECT: SW4.1, U8.16 (GPIO46)
/BTN_UP: SW1.1, U8.37 (U0TXD/GPIO43/CLK_OUT1)
/CKV: U6.7 (CKV), U8.25 (GPIO48/SPICLK_N/SUBSPICLK_N_DIFF)
/D0: U6.14 (D0), U8.5 (GPIO5/TOUCH5/ADC1_CH4)
/D1: U6.15 (D1), U8.6 (GPIO6/TOUCH6/ADC1_CH5)
/D2: U6.16 (D2), U8.7 (GPIO7/TOUCH7/ADC1_CH6)
/D3: U6.17 (D3), U8.8 (GPIO15/U0RTS/ADC2_CH4/XTAL_32K_P)
/D4: U6.18 (D4), U8.9 (GPIO16/U0CTS/ADC2_CH5/XTAL_32K_NH5)
/D5: U6.19 (D5), U8.10 (GPIO17/U1TXD/ADC2_CH6)
/D6: U6.20 (D6), U8.11 (GPIO18/U1RXD/ADC2_CH7/CLK_OUT3)
/D7: U6.21 (D7), U8.12 (GPIO8/TOUCH8/ADC1_CH7/SUBSPICS1)
/D8: U6.23 (D8), U8.17 (GPIO9/TOUCH9/ADC1_CH8/FSPIHD/SUBSPIHD)
/D9: U6.24 (D9), U8.18 (GPIO10/TOUCH10/ADC1_CH9/FSPICS0/FSPIIO4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)
/D10: U6.25 (D10), U8.19 (GPIO11/TOUCH11/ADC2_CH0/FSPID/FSPIIO5/S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)
/D11: U6.26 (D11), U8.20 (GPIO12/TOUCH12/ADC2_CH1/FSPICLK/FSPIIO6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)
/D12: U6.27 (D12), U8.21 (GPIO13/TOUCH13/ADC2_CH2/FSPIQ/FSPIIO7/S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)
/D13: U6.28 (D13), U8.22 (GPIO14/TOUCH14/ADC2_CH3/FSPIWP/FSPIDQS/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)
/D14: U6.29 (D14), U8.23 (GPIO21)
/D15: U6.30 (D15), U8.24 (GPIO47/SPICLK_P/SUBSPICLK_P_DIFF)
/EN: C14.2, C15.1, R10.1, R31.1, R32.2, U8.3 (EN)
/EP_MODE: U2.14 (IO1_1), U6.6 (Mode)
/EP_OE: U2.13 (IO1_0), U6.33 (XOE)
/EP_STV: U6.8 (SPV), U8.26 (GPIO45)
/EP_VCOM: C5.2, C38.1, R30.1, U3.15 (VCOM), U6.10 (VCOM)
/ESP_USB+: J9.A6 (D+), J9.B6 (D+), U8.14 (GPIO20/U1CTS/ADC2_CH9/CLK_OUT1/USB_D+)
/ESP_USB-: J9.A7 (D-), J9.B7 (D-), U8.13 (GPIO19/U1RTS/ADC2_CH8/CLK_OUT2/USB_D-)
/EXT1: J2.6, U2.5 (IO0_1)
/GPIO_35: U8.28 (SPIIO6/GPIO35/FSPID/SUBSPID)
/GPIO_36: U8.29 (SPIIO7/GPIO36/FSPICLK/SUBSPICLK)
/GPIO_37: U8.30 (SPIDQS/GPIO37/FSPIQ/SUBSPIQ)
/IO0: C41.2, R15.1, SW5.2, U8.27 (GPIO0/BOOT)
/LEH: U6.32 (XLE), U8.35 (MTMS/GPIO42)
/QWIIC_PWR_EN: U8.15 (GPIO3/TOUCH3/ADC1_CH2), U10.3 (EN)
/SCL: IC2.A3 (SCL), J2.4, J3.1, R6.2, U2.22 (SCL), U3.17 (SCL), U4.8 (SCL), U8.33 (MTDO/GPIO40/CLK_OUT2)
/SDA: IC2.A2 (SDA), J2.3, J3.2, R4.2, U2.23 (SDA), U3.18 (SDA), U4.2 (SDA), U8.32 (MTCK/GPIO39/CLK_OUT3/SUBSPICS1)
/TPS_PWRUP: U2.16 (IO1_3), U3.21 (PWRUP)
/TPS_PWR_GOOD: R14.2, U2.19 (IO1_6), U3.23 (PWR_GOOD)
/TPS_VCOM_CTRL: U2.17 (IO1_4), U3.12 (VCOM_CTRL)
/TPS_WAKEUP: U2.18 (IO1_5), U3.5 (WAKEUP)
/TPS_nINT: R16.2, U2.20 (IO1_7), U3.2 (NINT)
/VNEG_IN: C1.1, C7.1, C24.1, D1.2 (A), U3.4 (VNEG_IN), U3.16 (VCOM_PWR), U3.22 (PBKG), U3.26 (VN), U3.27 (VEE_IN), U3.49 (EPAD)
/XCL: U6.13 (XCL), U8.4 (GPIO4/TOUCH4/ADC1_CH3)
/XSTL: U6.31 (XSTL), U8.34 (MTDI/GPIO41/CLK_OUT1)
/~GPIO_INTR: R33.2, U2.1 (~INT), U8.31 (GPIO38/FSPIWP/SUBSPIWP)
EPD_VDD: C19.1, U3.46 (V3P3), U6.5 (VDD), U6.11 (VDD), U6.34 (TEST)
unnamed: D1.1 (K), L1.1, U3.25 (VN_SW)
unnamed: C20.1, D2.2 (A), D3.1 (K)
unnamed: C30.1, D2.1 (K), U3.30 (VEE_D)
unnamed: D4.2 (A), L2.2, U3.40 (VB_SW)
unnamed: C26.2, C28.2, D4.1 (K), U3.37 (VDDH_IN), U3.42 (VB), U3.43 (VPOS_IN)
unnamed: C29.2, D5.2 (A), U3.34 (VDDH_D)
unnamed: C25.1, D5.1 (K), D6.2 (A)
unnamed: D8.1 (K), R3.2
unnamed: D9.1 (K), R8.2
unnamed: D8.2 (A), D9.2 (A), D10.1 (K), U11.4 (VCC), U11.8 (CE)
unnamed: IC1.4 (PR1), R2.2, R17.1
unnamed: IC2.B1 (BIN), R37.2
unnamed: C16.1, IC2.B3 (VDD)
unnamed: J9.A5 (CC1), R13.1
unnamed: J9.B5 (CC2), R12.1
unnamed: Q3.3 (D), Q4.1 (G), R7.2
unnamed: R1.2, SW1.2
unnamed: R21.2, SW3.2
unnamed: R22.2, SW4.2
unnamed: R32.1, SW2.1
unnamed: R5.1, U2.21 (A0)
unnamed: C4.2, U3.7 (INT_LDO)
unnamed: R18.2, TH1.1, U3.47 (TS)
unnamed: C25.2, U3.36 (VDDH_DRV)
unnamed: R23.2, R24.1, U3.33 (VDDH_FB)
unnamed: C20.2, U3.28 (VEE_DRV)
unnamed: R19.2, R20.1, U3.31 (VEE_FB)
unnamed: C11.2, U3.1 (VREF)
unnamed: R9.2, U11.2 (PROG)
unnamed: R8.1, U11.7 (~CHRG)
unnamed: R3.1, U11.6 (~STDBY)
PWR_HOLD: Q3.1 (G), R11.1, U8.38 (GPIO2/TOUCH2/ADC1_CH1)
PWR_STATE: IC1.8 (ST), R35.2, U2.6 (IO0_2)
QWIIC_3V3: C39.2, J3.3, JP3.1 (A), U10.5 (VOUT)
RTC_INT: Q2.1 (G), U4.3 (~INT), U8.39 (GPIO1/TOUCH1/ADC1_CH0)
VIN: C2.1, C6.2, C9.1, C10.2, C12.1, C21.1, C32.2, IC1.2 (VOUT_1), IC1.7 (VOUT_2), L2.1, U1.3 (VI), U3.10 (VIN), U3.24 (VIN_P), U10.1 (VIN)
VIN2: C13.2, IC1.6 (VIN2), Q2.3 (D), Q4.3 (D), SW6.2

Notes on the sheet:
QWIIC Connector
Misc.
EPD Power
GPIO Expander with EPD + Power Controls
Fuel Gauge + Battery
ESP32 S3 Module
USB-C JTAG / CDC Serial to MCU
OCTAL PSRAM DO NOT *USE*
EPD Connector (16-bit Bus)
Power 3.3V - MCU + TPS65185 + PCA IO expander
WAKE /RST switch (200 ms)
IO0 BOOT / USR BUTON
JST ZH 1.5mm
3 push buttons
EXTRA Power 3.3V - Close to QWIIC
LiPo Charging
Close to EPD connector
External RTC deep-sleep circuit
APP Note: https://www.microcrystal.com/fileadmin/Media/Products/RTC/App.Manual/RV-3032-C7_App-Manual.pdf Tested by Simon
NOTE: IO46 on HIGH won't let you flash the S3 MCU

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

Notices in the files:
epdiy-v7-light/epdiy-v7-light.kicad_sch:
License: CC-BY-SA-4.0
parts and their libraries:
Copyright 2016 Accelerated Designs. All rights reserved.
Copyright 2021 Accelerated Designs. All rights reserved.
